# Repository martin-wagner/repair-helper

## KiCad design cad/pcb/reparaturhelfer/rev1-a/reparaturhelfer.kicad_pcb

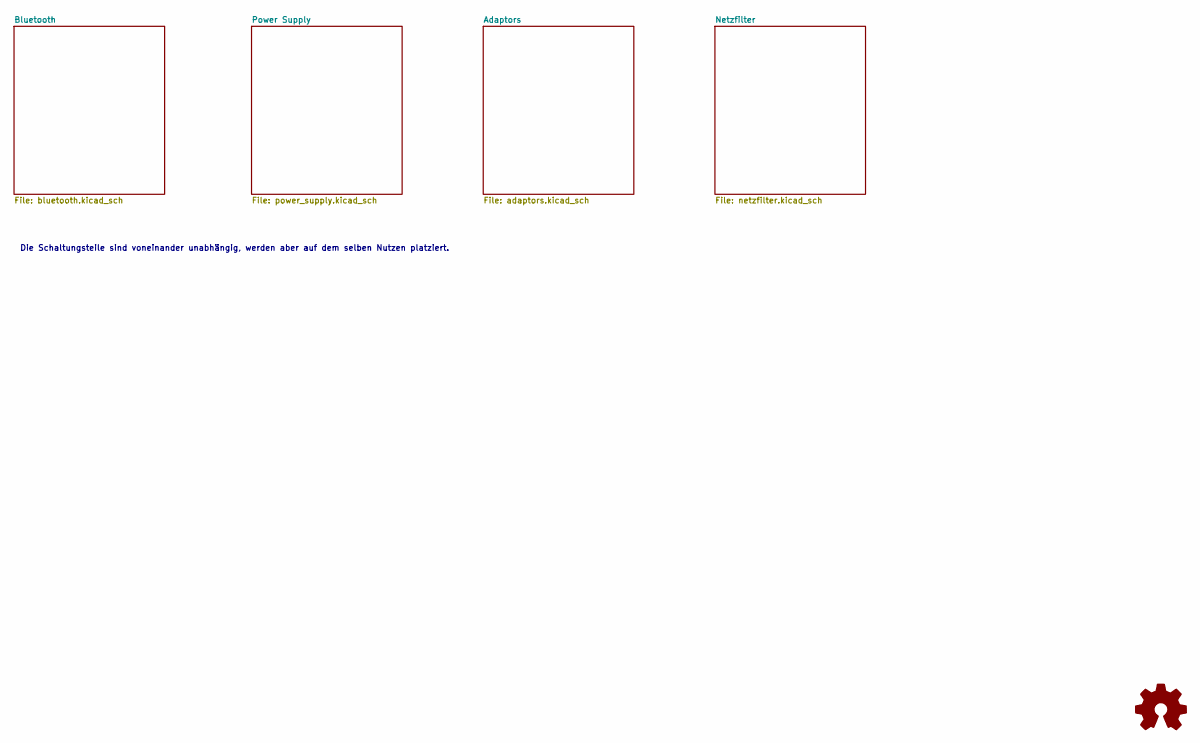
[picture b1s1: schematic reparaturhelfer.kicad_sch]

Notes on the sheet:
Die Schaltungsteile sind voneinander unabhängig, werden aber auf dem selben Nutzen platziert.

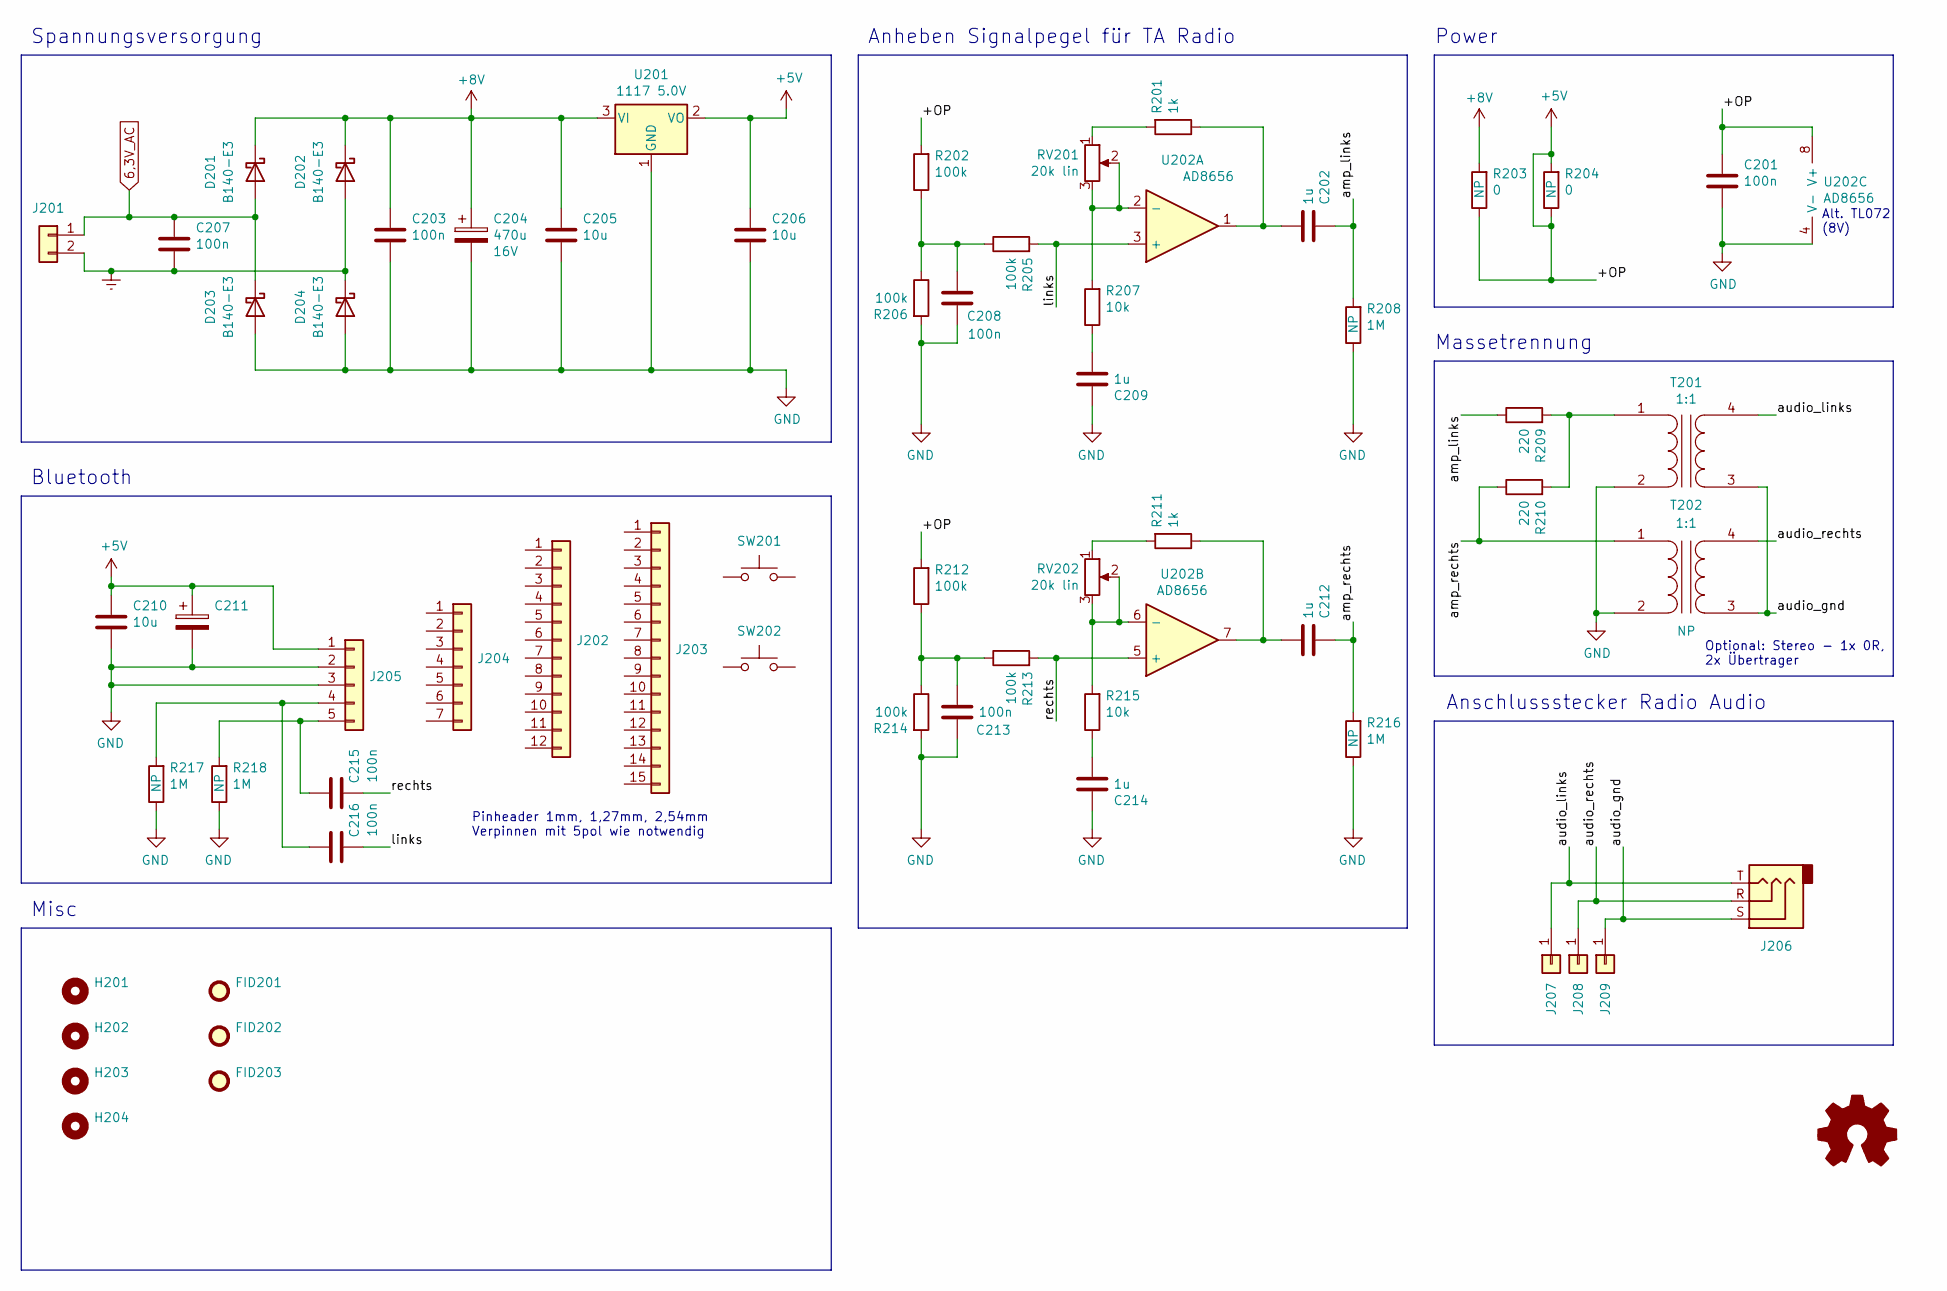
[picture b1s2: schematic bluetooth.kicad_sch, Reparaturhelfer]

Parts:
C201, C203, C207, C208, C213, C215, C216: 100n; C_0603_1608Metric
C202, C209, C212, C214: 1u; C_0805_2012Metric
C204: 470u; CP_Radial_D8.0mm_P5.00mm; Voltage 16V
C205, C206, C210: 10u; C_1206_3216Metric
C211: CP_Radial_D5.0mm_P2.50mm
D201, D202, D203, D204: B140-E3; D_SMA
FID201, FID202, FID203: Fiducial; Fiducial_1mm_Mask2mm
H201, H202, H203, H204: MountingHole; MountingHole_3.2mm_M3
J201: Conn_01x02; PinHeader_1x02_P2.54mm_Vertical
J202: Conn_01x12; PinHeader_1x12_P1.27mm_Vertical
J203: Conn_01x15; PinHeader_1x15_P1.00mm_Vertical
J204: Conn_01x07; PinHeader_1x07_P2.54mm_Vertical
J205: Conn_01x05; PinHeader_1x05_P2.54mm_Vertical
J206: AudioJack3; Jack_3.5mm_CUI_SJ1-3523N_Horizontal
J207, J208, J209: Conn_01x01; PinHeader_1x01_P2.54mm_Vertical
R201, R211: 1k; R_0603_1608Metric
R202, R205, R206, R212, R213, R214: 100k; R_0603_1608Metric
R203, R204: 0; R_0603_1608Metric
R207, R215: 10k; R_0603_1608Metric
R208, R216, R217, R218: 1M; R_0603_1608Metric
R209, R210: 220; R_0603_1608Metric
RV201, RV202: 20k lin; Potentiometer_Vishay_TS53YJ_Vertical
SW201, SW202: SW_Push; SW_PUSH_6mm
T201, T202: 1:1; Transformer_NF_EI14
U201: 1117 5.0V; TO-252-3_TabPin2
U202: AD8656; SOIC-8_3.9x4.9mm_P1.27mm

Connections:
6,3V_AC: C207.1, D201.2 (A), D203.1 (K), J201.1
+5V: C201.1, C206.1, C210.1, C211.1, J205.1, R202.2, R203.1, R204.1, R204.2, R212.2, U201.2 (VO), U202.8 (V+)
+8V: C203.1, C204.1, C205.1, D201.1 (K), D202.1 (K), R203.2, U201.3 (VI)
/Bluetooth/amp_links: C202.1, R208.2, R209.1
/Bluetooth/amp_rechts: C212.1, R210.1, R216.2, T202.1 (AA)
/Bluetooth/audio_gnd: J206.S, J209.1, T201.3 (SA), T202.3 (SA)
/Bluetooth/audio_links: J206.T, J207.1, T201.4 (SB)
/Bluetooth/audio_rechts: J206.R, J208.1, T202.4 (SB)
/Bluetooth/links: C216.1, R205.2, U202.3 (+)
/Bluetooth/rechts: C215.1, R213.2, U202.5 (+)
Earth: C207.2, D202.2 (A), D204.1 (K), J201.2; also elsewhere on the board
GND: C201.2, C203.2, C204.2, C205.2, C206.2, C208.1, C209.1, C210.2, C211.2, C213.2, C214.1, D203.2 (A), D204.2 (A), J205.2, J205.3, R206.2, R208.1, R214.2, R216.1, R217.1, R218.1, T201.2 (AB), T202.2 (AB), U201.1 (GND), U202.4 (V-)
unnamed: C202.2, R201.1, U202.1
unnamed: C208.2, R202.1, R205.1, R206.1
unnamed: C209.2, R207.1
unnamed: C212.2, R211.1, U202.7
unnamed: C213.1, R212.1, R213.1, R214.1
unnamed: C214.2, R215.1
unnamed: C216.2, J205.4, R217.2
unnamed: C215.2, J205.5, R218.2
unnamed: R201.2, RV201.1
unnamed: R211.2, RV202.1
unnamed: R209.2, R210.2, T201.1 (AA)
unnamed: R207.2, RV201.2, RV201.3, U202.2 (-)
unnamed: R215.2, RV202.2, RV202.3, U202.6 (-)

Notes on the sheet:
Anheben Signalpegel für TA Radio
Anschlussstecker Radio Audio
Power
Optional: Stereo - 1x 0R, 2x Übertrager
Massetrennung
Alt. TL072 (8V)
Pinheader 1mm, 1,27mm, 2,54mm Verpinnen mit 5pol wie notwendig
Misc
Spannungsversorgung
Bluetooth

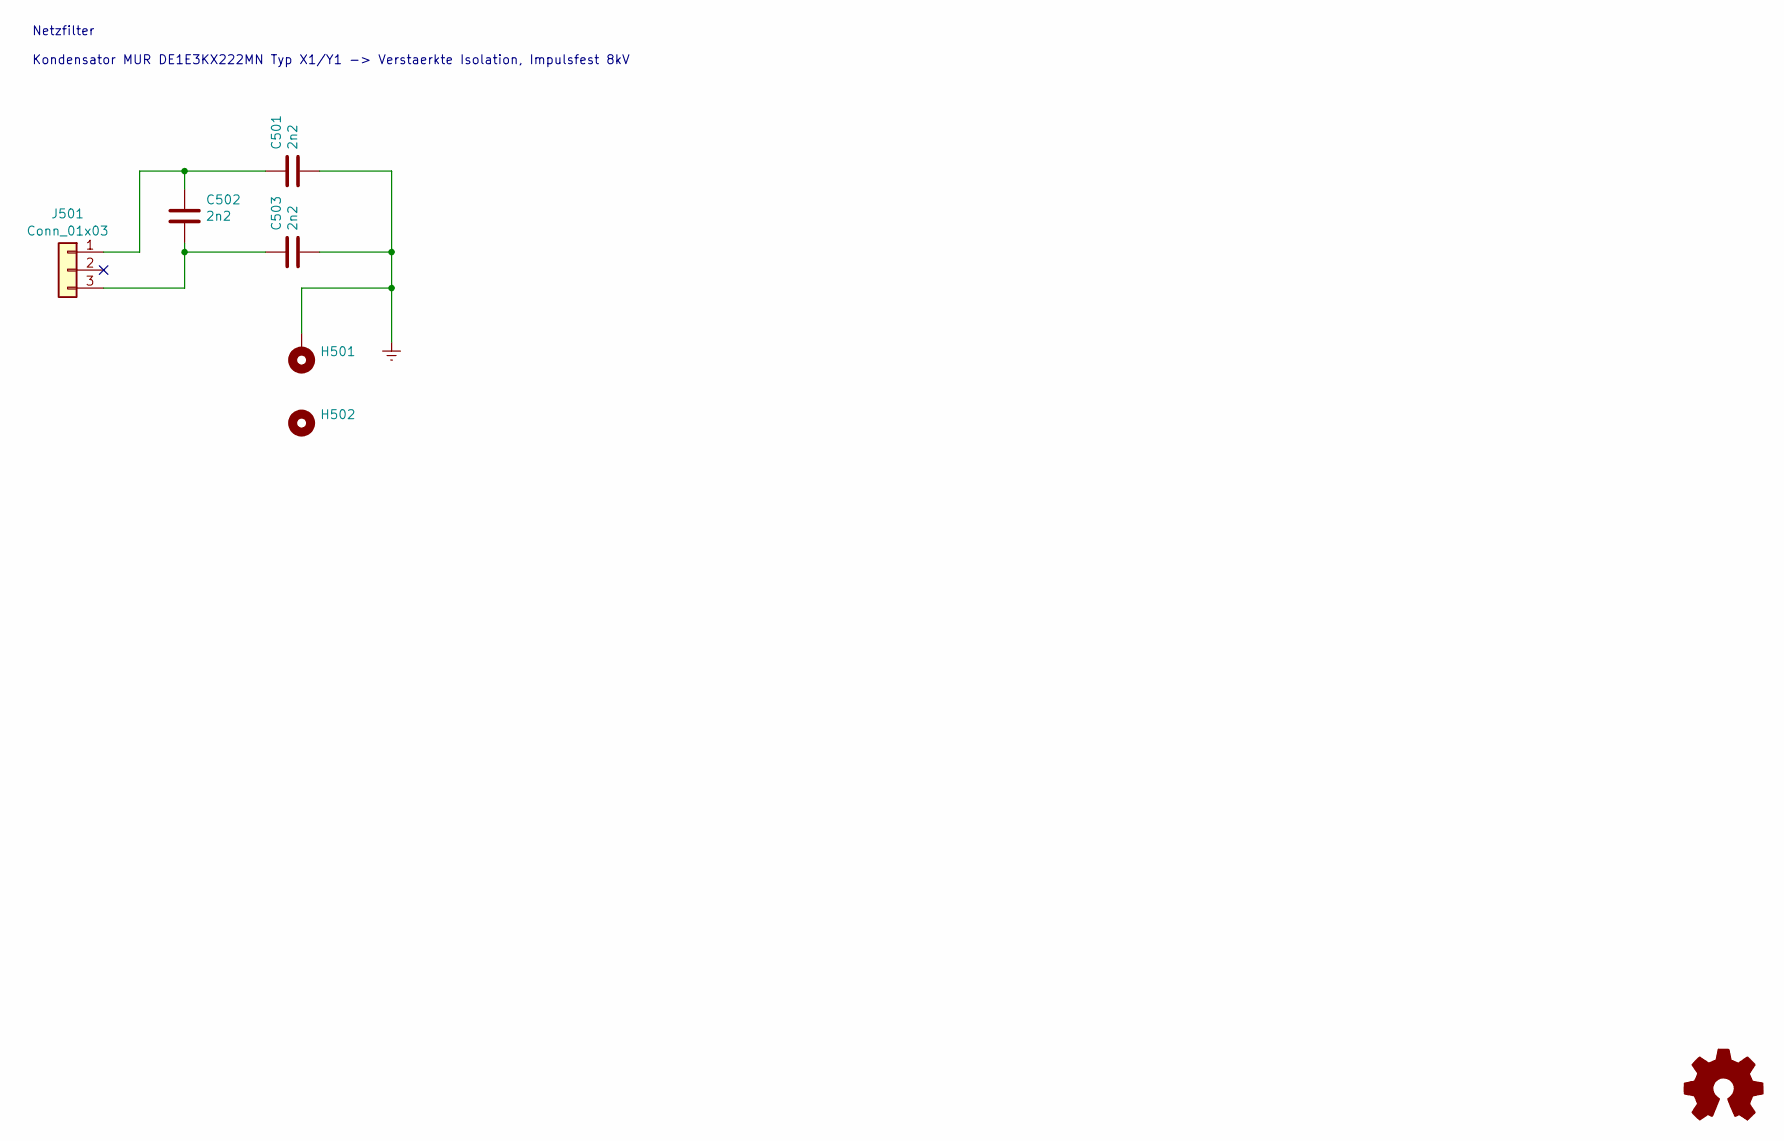
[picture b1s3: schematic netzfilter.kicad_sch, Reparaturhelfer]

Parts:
C501, C502, C503: 2n2; C_Disc_D11.0mm_W5.0mm_P10.00mm
H501: MountingHole_Pad; MountingHole_3.2mm_M3_Pad
H502: MountingHole; MountingHole_3.2mm_M3
J501: Conn_01x03; PinHeader_1x03_P2.54mm_Vertical

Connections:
Earth: C501.2, C503.2, H501.1; also elsewhere on the board
unnamed: C501.1, C502.1, J501.1
unnamed: C502.2, C503.1, J501.3

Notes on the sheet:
Netzfilter Kondensator MUR DE1E3KX222MN Typ X1/Y1 -> Verstaerkte Isolation, Impulsfest 8kV

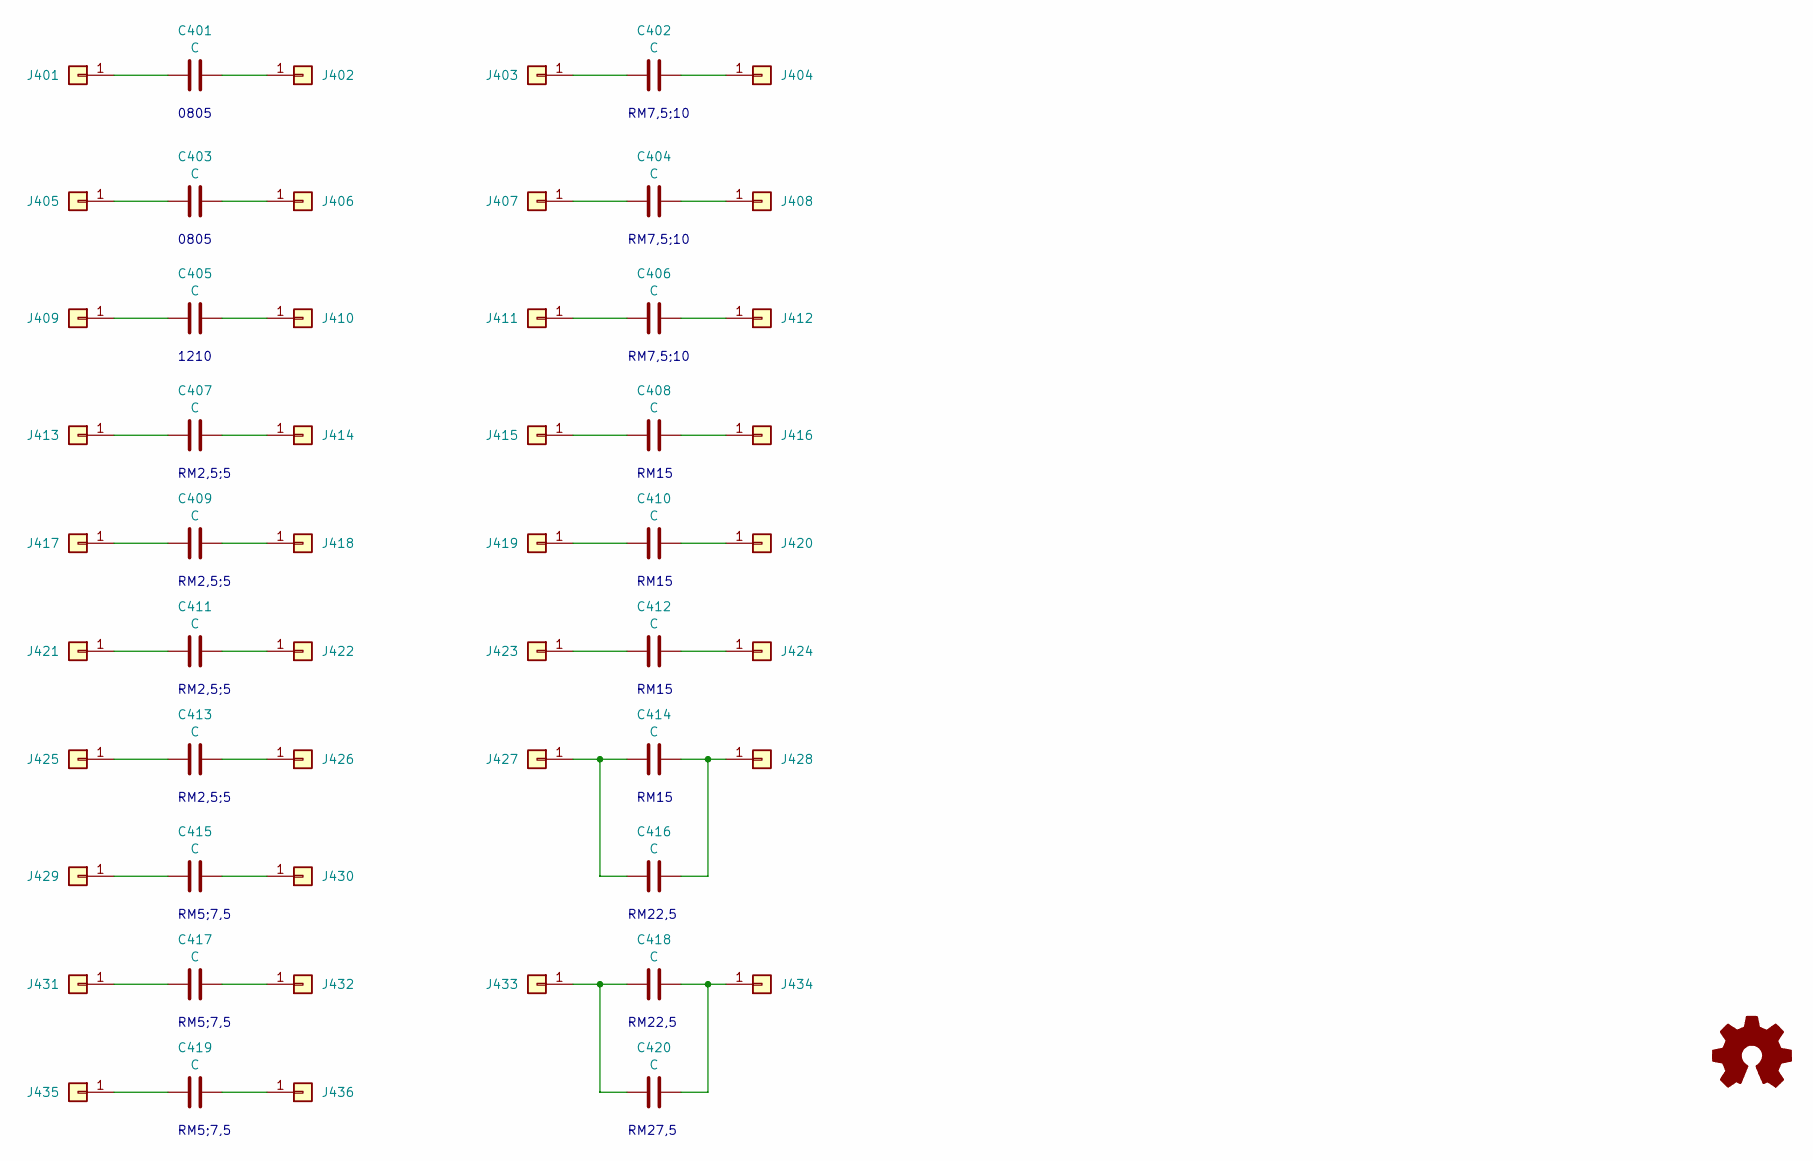
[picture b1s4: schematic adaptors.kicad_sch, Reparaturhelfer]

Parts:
C401, C403: C; C_0805_2012Metric_Pad1.18x1.45mm_HandSolder
C402, C404, C406: C; C_Rect_L13.0mm_W6.5mm_P7.50mm_P10.00mm
C405: C; C_1210_3225Metric_Pad1.33x2.70mm_HandSolder
C407, C409, C411, C412, C413: C; C_Rect_L7.0mm_W3.5mm_P2.50mm_P5.00mm
C408, C410, C414: C; C_Rect_L16.5mm_W7.0mm_P15.00mm_MKT
C415, C417, C419: C; C_Rect_L10.0mm_W5.0mm_P5.00mm_P7.50mm
C416, C418: C; C_Rect_L24.0mm_W10.1mm_P22.50mm_MKT
C420: C; C_Rect_L29.0mm_W11.0mm_P27.50mm_MKT
J401, J402, J403, J404, J405, J406, J407, J408, J409, J410, J411, J412, J413, J414, J415, J416, J417, J418, J419, J420, J421, J422, J423, J424, J425, J426, J427, J428, J429, J430, J431, J432, J433, J434, J435, J436: Conn_01x01; PinHeader_1x01_P2.54mm_Vertical

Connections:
unnamed: C401.1, J401.1
unnamed: C401.2, J402.1
unnamed: C402.1, J403.1
unnamed: C402.2, J404.1
unnamed: C403.1, J405.1
unnamed: C403.2, J406.1
unnamed: C404.1, J407.1
unnamed: C404.2, J408.1
unnamed: C405.1, J409.1
unnamed: C405.2, J410.1
unnamed: C406.1, J411.1
unnamed: C406.2, J412.1
unnamed: C407.1, J413.1
unnamed: C407.2, J414.1
unnamed: C408.1, J415.1
unnamed: C408.2, J416.1
unnamed: C409.1, J417.1
unnamed: C409.2, J418.1
unnamed: C410.1, J419.1
unnamed: C410.2, J420.1
unnamed: C411.1, J421.1
unnamed: C411.2, J422.1
unnamed: C412.1, J423.1
unnamed: C412.2, J424.1
unnamed: C413.1, J425.1
unnamed: C413.2, J426.1
unnamed: C414.1, C416.1, J427.1
unnamed: C414.2, C416.2, J428.1
unnamed: C415.1, J429.1
unnamed: C415.2, J430.1
unnamed: C417.1, J431.1
unnamed: C417.2, J432.1
unnamed: C418.1, C420.1, J433.1
unnamed: C418.2, C420.2, J434.1
unnamed: C419.1, J435.1
unnamed: C419.2, J436.1

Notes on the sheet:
RM7,5;10
0805
RM5;7,5
RM15
RM2,5;5
RM22,5
1210
RM27,5

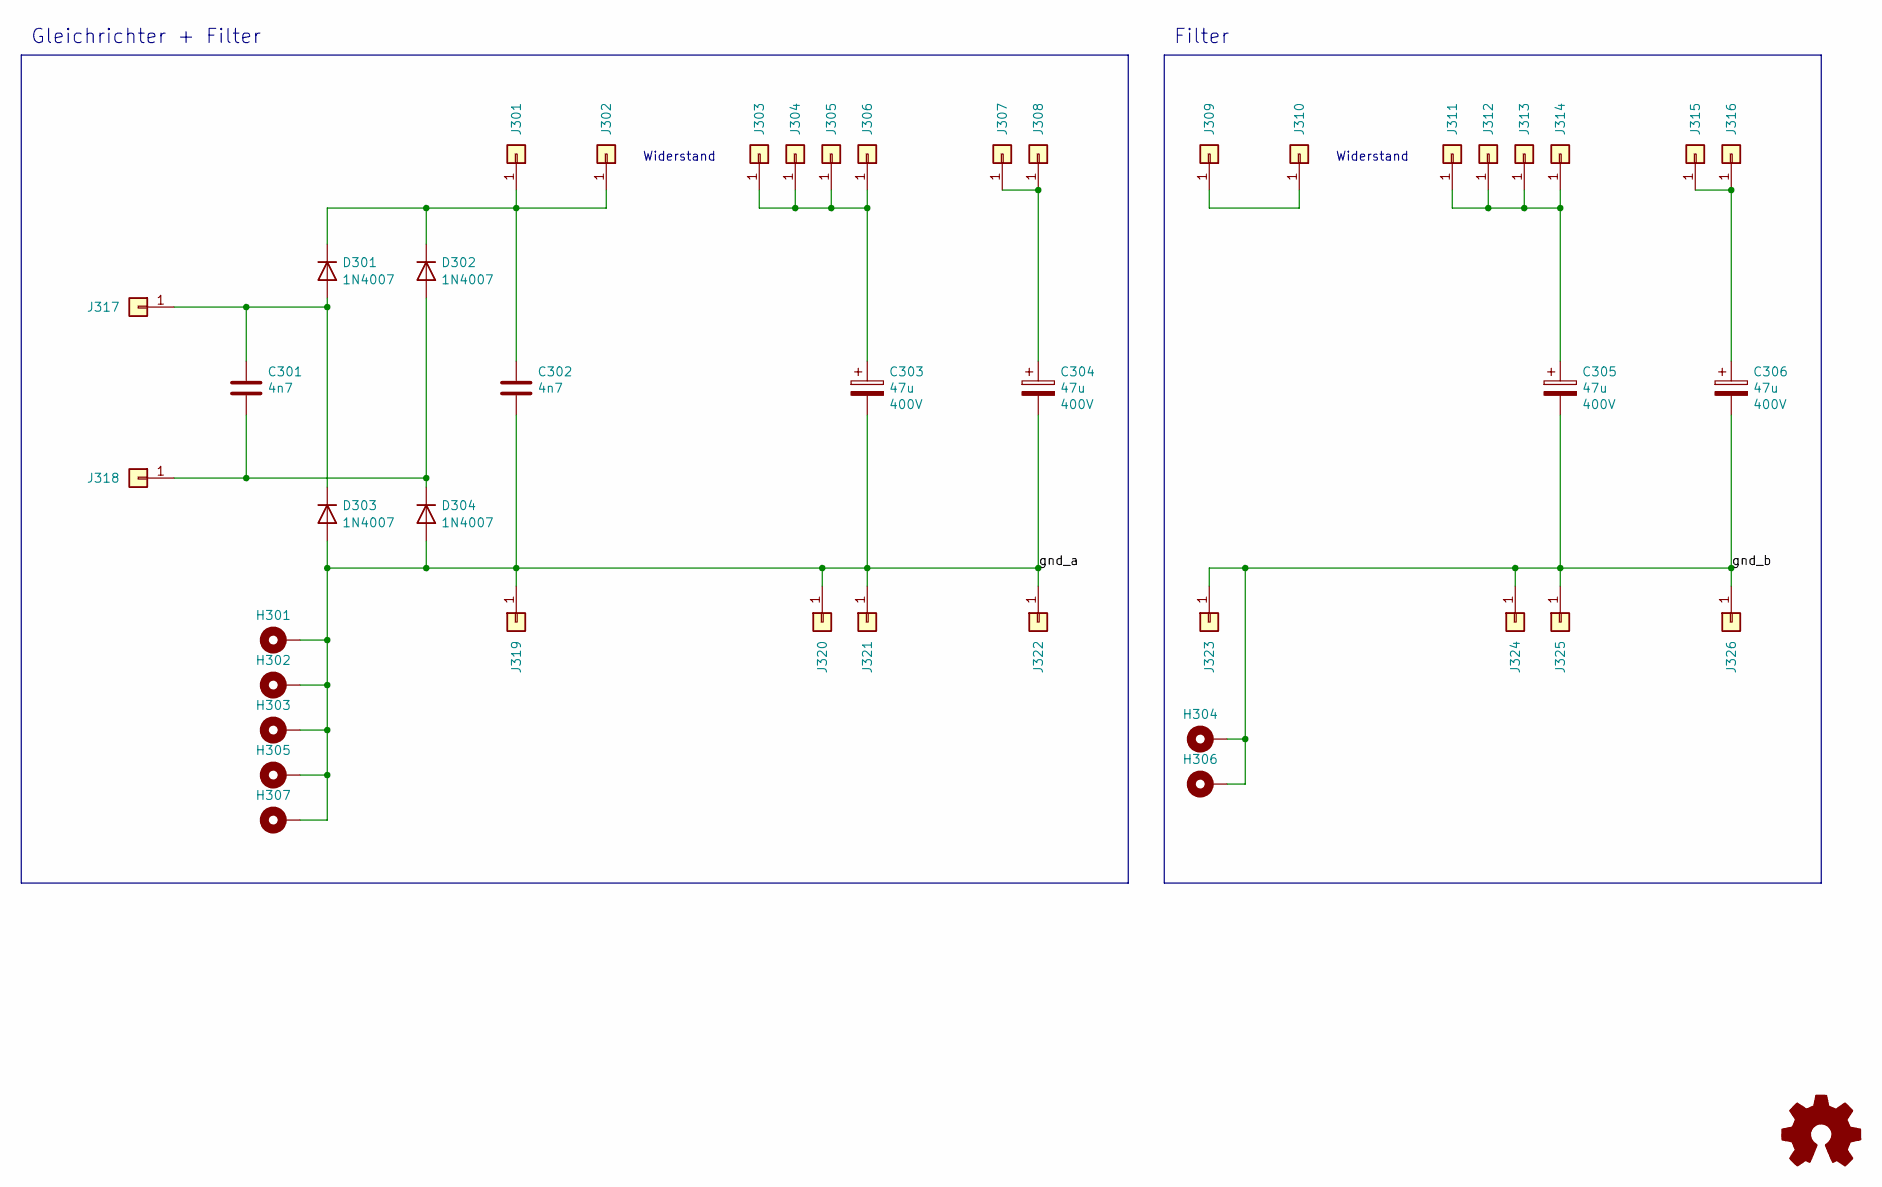
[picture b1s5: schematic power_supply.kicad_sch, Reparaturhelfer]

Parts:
C301, C302: 4n7; C_Rect_L13.0mm_W3.0mm_P10.00mm_FKS3_FKP3_MKS4
C303, C304, C305, C306: 47u; CP_Radial_D16.0mm_P7.50mm; Voltage 400V
D301, D302, D303, D304: 1N4007; D_A-405_P10.16mm_Horizontal
H301, H302, H303, H304, H305, H306, H307: MountingHole_Pad; MountingHole_3.2mm_M3_Pad
J301, J302, J303, J304, J305, J306, J307, J308, J309, J310, J311, J312, J313, J314, J315, J316, J317, J318, J319, J320, J321, J322, J323, J324, J325, J326: Conn_01x01; PinHeader_1x01_P2.54mm_Vertical

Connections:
/Power Supply/gnd_a: C302.2, C303.2, C304.2, D303.2 (A), D304.2 (A), H301.1, H302.1, H303.1, H305.1, H307.1, J319.1, J320.1, J321.1, J322.1
/Power Supply/gnd_b: C305.2, C306.2, H304.1, H306.1, J323.1, J324.1, J325.1, J326.1
unnamed: C301.1, D301.2 (A), D303.1 (K), J317.1
unnamed: C302.1, D301.1 (K), D302.1 (K), J301.1, J302.1
unnamed: C301.2, D302.2 (A), D304.1 (K), J318.1
unnamed: C303.1, J303.1, J304.1, J305.1, J306.1
unnamed: C304.1, J307.1, J308.1
unnamed: J309.1, J310.1
unnamed: C305.1, J311.1, J312.1, J313.1, J314.1
unnamed: C306.1, J315.1, J316.1

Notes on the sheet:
Widerstand
Gleichrichter + Filter
Filter

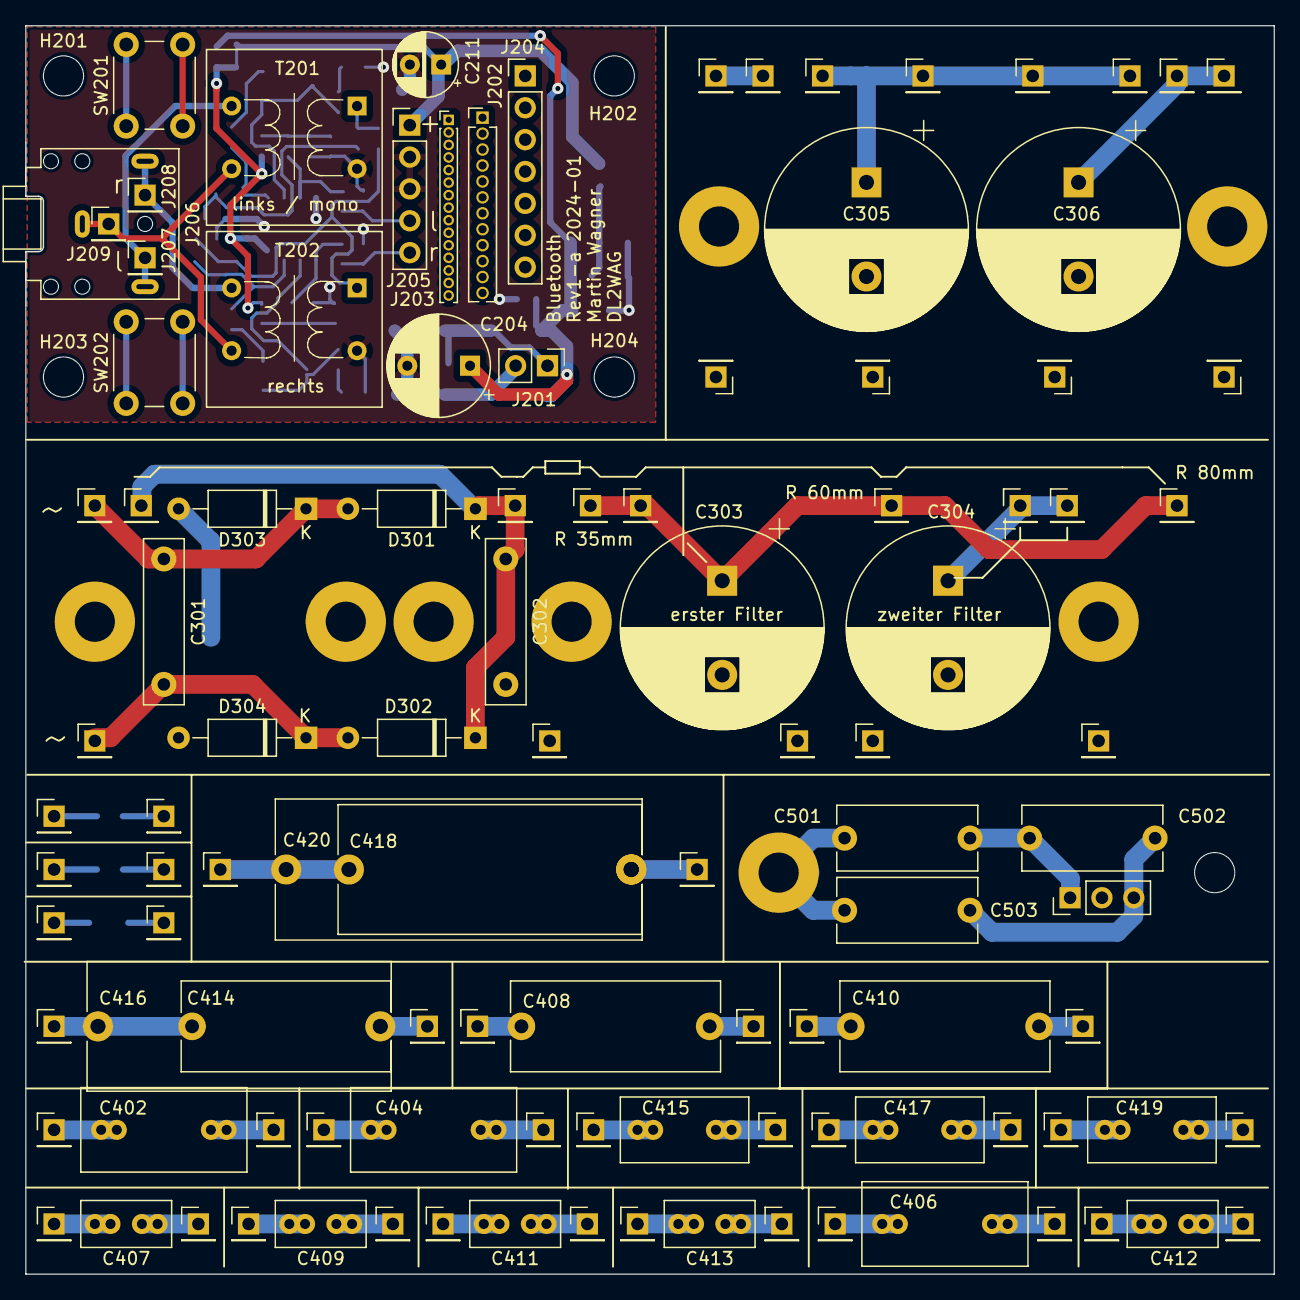
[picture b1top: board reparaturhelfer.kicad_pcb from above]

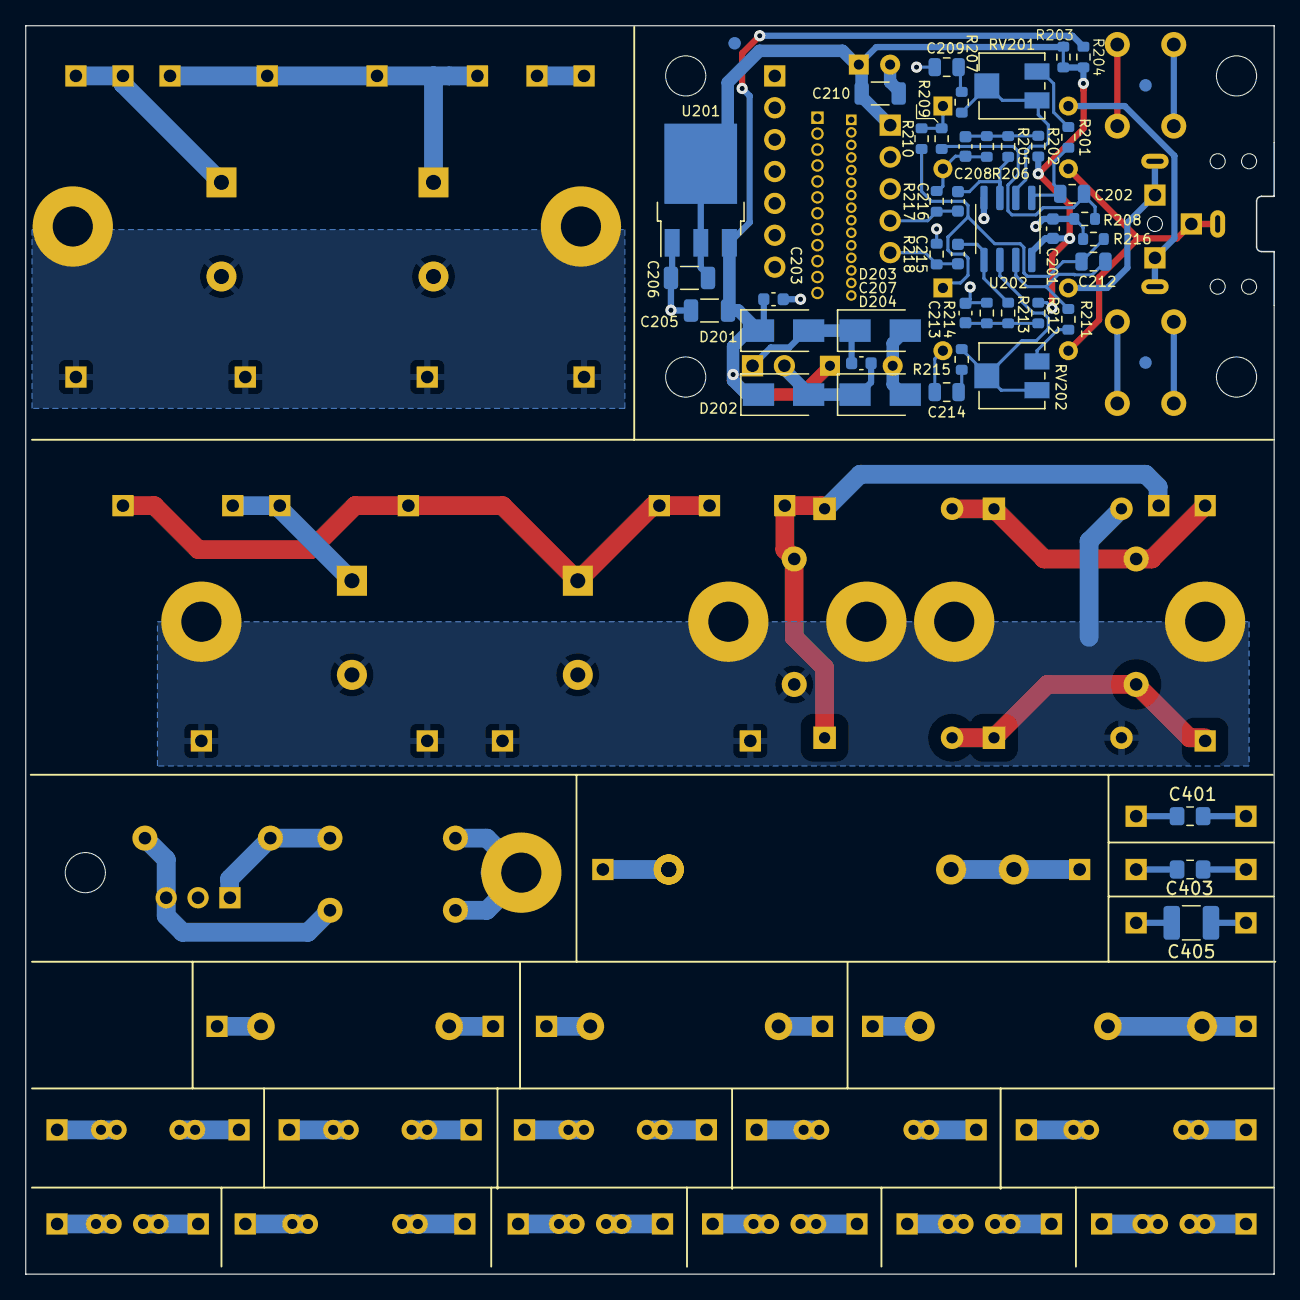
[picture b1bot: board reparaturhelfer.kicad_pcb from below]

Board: 2 copper layers, 99.5 x 99.5 mm, 167 parts (46 on the bottom side), 73 nets.

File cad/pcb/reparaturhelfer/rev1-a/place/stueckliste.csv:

"Source:","/home/martin/elektronik/radios/reparaturhelfer/cad/pcb/reparaturhelfer/rev1-a/reparaturhelfer.kicad_sch"
"Date:","Mon 08 Jan 2024 13:20:33 CET"
"Tool:","Eeschema 7.0.10-7.0.10~ubuntu22.04.1"
"Generator:","/usr/share/kicad/plugins/bom_csv_grouped_by_value.py"
"Component Count:","167"

"Collated Components:"

"Item","Qty","Reference(s)","Value","LibPart","Footprint","Datasheet","DNP","Bauteil","Placement","Voltage"
"1","7","C201, C203, C207, C208, C213, C215, C216","100n","Device:C","Capacitor_SMD:C_0603_1608Metric","~","","WE 885382206004","",""
"2","4","C202, C209, C212, C214","1u","Device:C","Capacitor_SMD:C_0805_2012Metric","~","","WE 885012207078","",""
"3","1","C204","470u","saba-fernbedienung-rescue:CP-Device","Capacitor_THT:CP_Radial_D8.0mm_P5.00mm","","","","","16V"
"4","3","C205, C206, C210","10u","Device:C","Capacitor_SMD:C_1206_3216Metric","~","","WE 885012208069","",""
"5","1","C211","~","saba-fernbedienung-rescue:CP-Device","Capacitor_THT:CP_Radial_D5.0mm_P2.50mm","","","","",""
"6","2","C301, C302","4n7","Device:C","Capacitor_THT:C_Rect_L13.0mm_W3.0mm_P10.00mm_FKS3_FKP3_MKS4","~","","MKS4 4700/1000","",""
"7","4","C303, C304, C305, C306","47u","saba-fernbedienung-rescue:CP-Device","Capacitor_THT:CP_Radial_D16.0mm_P7.50mm","","","","","400V"
"8","2","C401, C403","C","Device:C","Capacitor_SMD:C_0805_2012Metric_Pad1.18x1.45mm_HandSolder","~","","","",""
"9","3","C402, C404, C406","C","Device:C","Capacitor_THT:C_Rect_L13.0mm_W6.5mm_P7.50mm_P10.00mm","~","","","",""
"10","1","C405","C","Device:C","Capacitor_SMD:C_1210_3225Metric_Pad1.33x2.70mm_HandSolder","~","","","",""
"11","5","C407, C409, C411, C412, C413","C","Device:C","Capacitor_THT:C_Rect_L7.0mm_W3.5mm_P2.50mm_P5.00mm","~","","","",""
"12","3","C408, C410, C414","C","Device:C","Capacitor_THT:C_Rect_L16.5mm_W7.0mm_P15.00mm_MKT","~","","","",""
"13","3","C415, C417, C419","C","Device:C","Capacitor_THT:C_Rect_L10.0mm_W5.0mm_P5.00mm_P7.50mm","~","","","",""
"14","2","C416, C418","C","Device:C","Capacitor_THT:C_Rect_L24.0mm_W10.1mm_P22.50mm_MKT","~","","","",""
"15","1","C420","C","Device:C","Capacitor_THT:C_Rect_L29.0mm_W11.0mm_P27.50mm_MKT","~","","","",""
"16","3","C501, C502, C503","2n2","Device:C","Capacitor_THT:C_Disc_D11.0mm_W5.0mm_P10.00mm","~","","MUR DE1E3KX222MN","",""
"17","4","D201, D202, D203, D204","B140-E3","Diode:B140-E3","Diode_SMD:D_SMA","http://www.vishay.com/docs/88946/b120.pdf","","Vishay B140-E3/61T","",""
"18","4","D301, D302, D303, D304","1N4007","Device:D","Diode_THT:D_A-405_P10.16mm_Horizontal","~","","","",""
"19","3","FID201, FID202, FID203","Fiducial","Mechanical:Fiducial","Fiducial:Fiducial_1mm_Mask2mm","~","","","",""
"20","5","H201, H202, H203, H204, H502","MountingHole","Mechanical:MountingHole","MountingHole:MountingHole_3.2mm_M3","~","","","",""
"21","8","H301, H302, H303, H304, H305, H306, H307, H501","MountingHole_Pad","Mechanical:MountingHole_Pad","MountingHole:MountingHole_3.2mm_M3_Pad","~","","","",""
"22","1","J201","Conn_01x02","Connector_Generic:Conn_01x02","Connector_PinHeader_2.54mm:PinHeader_1x02_P2.54mm_Vertical","~","","","",""
"23","1","J202","Conn_01x12","Connector_Generic:Conn_01x12","Connector_PinHeader_1.27mm:PinHeader_1x12_P1.27mm_Vertical","~","","","",""
"24","1","J203","Conn_01x15","Connector_Generic:Conn_01x15","Connector_PinHeader_1.00mm:PinHeader_1x15_P1.00mm_Vertical","~","","","",""
"25","1","J204","Conn_01x07","Connector_Generic:Conn_01x07","Connector_PinHeader_2.54mm:PinHeader_1x07_P2.54mm_Vertical","~","","","",""
"26","1","J205","Conn_01x05","Connector_Generic:Conn_01x05","Connector_PinHeader_2.54mm:PinHeader_1x05_P2.54mm_Vertical","~","","","",""
"27","1","J206","AudioJack3","Connector:AudioJack3","Connector_Audio:Jack_3.5mm_CUI_SJ1-3523N_Horizontal","https://www.farnell.com/datasheets/2028381.pdf","","CLIFF FC68131","",""
"28","65","J207, J208, J209, J301, J302, J303, J304, J305, J306, J307, J308, J309, J310, J311, J312, J313, J314, J315, J316, J317, J318, J319, J320, J321, J322, J323, J324, J325, J326, J401, J402, J403, J404, J405, J406, J407, J408, J409, J410, J411, J412, J413, J414, J415, J416, J417, J418, J419, J420, J421, J422, J423, J424, J425, J426, J427, J428, J429, J430, J431, J432, J433, J434, J435, J436","Conn_01x01","Connector_Generic:Conn_01x01","Connector_PinHeader_2.54mm:PinHeader_1x01_P2.54mm_Vertical","~","","","",""
"29","1","J501","Conn_01x03","Connector_Generic:Conn_01x03","Connector_PinHeader_2.54mm:PinHeader_1x03_P2.54mm_Vertical","~","","","",""
"30","2","R201, R211","1k","Device:R","Resistor_SMD:R_0603_1608Metric","~","","","",""
"31","6","R202, R205, R206, R212, R213, R214","100k","Device:R","Resistor_SMD:R_0603_1608Metric","~","","","",""
"32","2","R203, R204","0","Device:R","Resistor_SMD:R_0603_1608Metric","~","","","NP",""
"33","2","R207, R215","10k","Device:R","Resistor_SMD:R_0603_1608Metric","~","","","",""
"34","4","R208, R216, R217, R218","1M","Device:R","Resistor_SMD:R_0603_1608Metric","~","","","NP",""
"35","2","R209, R210","220","Device:R","Resistor_SMD:R_0603_1608Metric","~","","","",""
"36","2","RV201, RV202","20k lin","saba-fernbedienung-rescue:R_POT-Device","Potentiometer_SMD:Potentiometer_Vishay_TS53YJ_Vertical","","","23A-20K","",""
"37","2","SW201, SW202","SW_Push","Switch:SW_Push","Button_Switch_THT:SW_PUSH_6mm","~","","","",""
"38","2","T201, T202","1:1","Device:Transformer_1P_1S","local:Transformer_NF_EI14","~","","","NP",""
"39","1","U201","1117 5.0V","Regulator_Linear:AP1117-50","Package_TO_SOT_SMD:TO-252-3_TabPin2","http://www.diodes.com/datasheets/AP1117.pdf","","LD1117DT50CTR","",""
"40","1","U202","AD8656","saba-fernbedienung-rescue:Opamp_Dual_Generic-Device","Package_SO:SOIC-8_3.9x4.9mm_P1.27mm","https://www.analog.com/media/en/technical-documentation/data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","","AD8656ARZ","",""

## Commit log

2024-01-04 Add: empty project
2024-01-04 Add: scm
2024-01-05 Add: Routing Bluetooth
2024-01-08 Add: PCB fertig
2024-01-08 add: Fertigungsdaten
